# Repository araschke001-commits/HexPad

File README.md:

# HexPad
This is a macropad with 6 keys, a rotary encoder, and an oled display. Almost everything in the cad file for this project is customizable. You can add as many keys as you want, change the dimensions of the usb c port, the inside dimensions, the wall dimensions, and basically everything else.

You would use my project by pressing the keys to perform specific functions on the computer, like a simple key press like the number 1, or later I might change it to open a site or type a password in. The rotary encoder is to change volume and mute/unmute it. The oled display is to indicate if a button was pressed/changed.

The reason why I made this project is to learn how to build things like this project so in the future I can make other things similar to this.

## Features:
- 3d printed case
- 6 keys (2 rows of 3)
- 0.91" OLED display
- Rotary encoder
- Almost everything is customizable for the CAD design.

## CAD Model:
It is put together with 4 M3 Screws that go directly into the plastic of the case.

It is made of 2 separate 3d printed parts, the top and the bottom.

Here is the share link to the project: https://cad.onshape.com/documents/888c45d35c64a39055184245/w/6328c76e156d93114c845f2d/e/f25f9ae1fe243c3fda6125d5?renderMode=0&uiState=69c88a6d89ef4c064d381a0c

CAD Model:

Made in Onshape.

## PCB:
This PCB was made in KiCad.

Schematic:

PCB:

In hindsight, I maybe should have used a matrix to wire the switches, but it was simpler not to.

## Firmware:
This project uses C++ as firmware because I was unable to get the QMK firmware to work and I already had experience writing code in C++ (I did have to look up how to do some of the arduino stuff though).

The 6 keys act as a partial number pad for now. The oled is to display the last action, and the rotary encoder is to change volume and mute/unmute it.

## BOM:
This should be everything needed for my hackpad:
- Seeed Studio XIAO RP2040	(1x)
- Cherry MX Keycap - R2 (Opaque Black)	(6x)
- Cherry MX Brown 55g Tactile Switch	(6x)
- 0.91" OLED Display (1x)
- Rotary Encoder (1x)
- Rotary Encoder Knob (1x)
- M3 x 8mm Socket Button Head Screws	(4x)
- USB-C to USB-A Cable (3ft)	(1x)
- Custom PCB
- 3d Printed Case

## Build Guide
1. Order the components
2. Order the PCB
3. Solder the components onto the board
4. Move the firmware to the board using Arduino IDE
5. Put the pcb with everything attached in the case
6. Screw on the lid to the case

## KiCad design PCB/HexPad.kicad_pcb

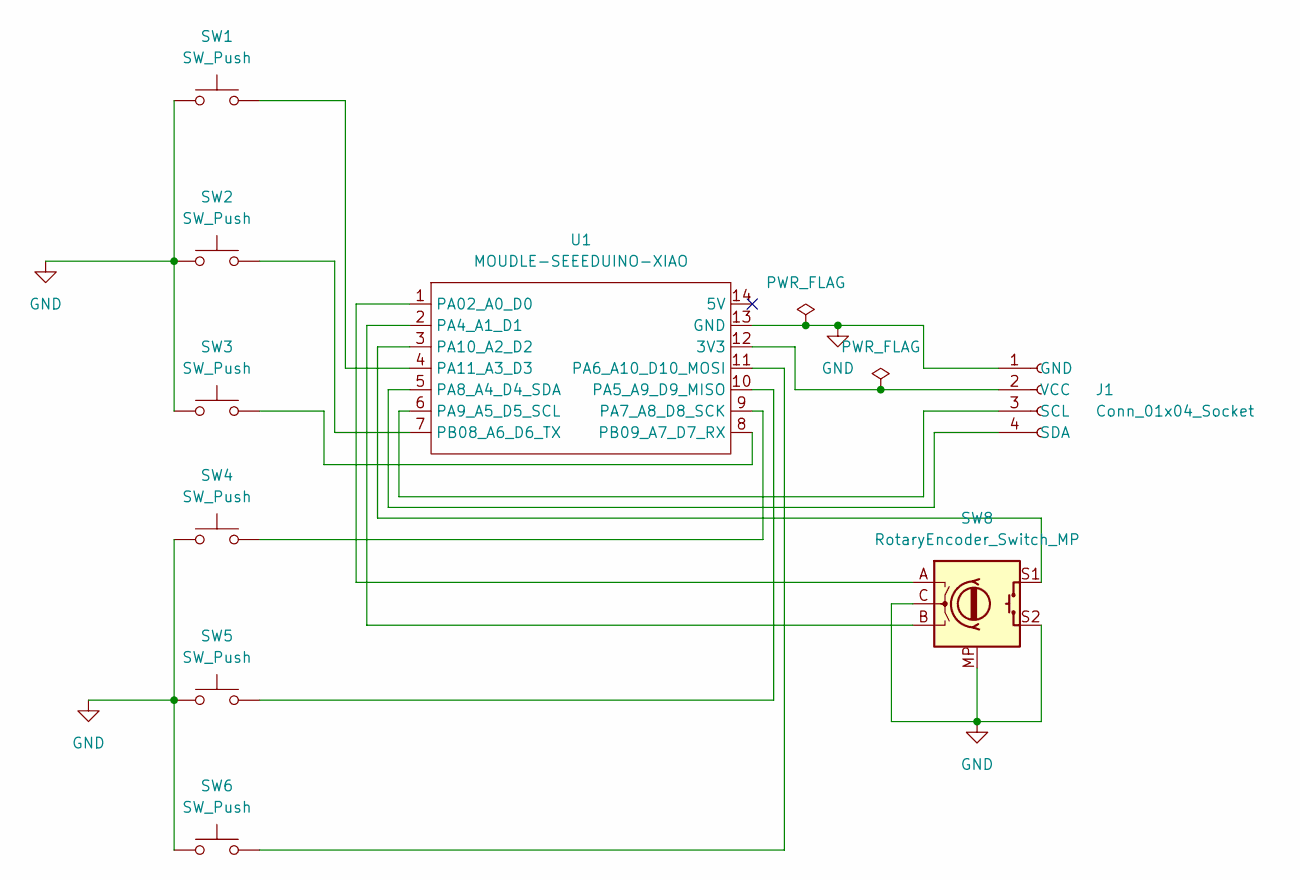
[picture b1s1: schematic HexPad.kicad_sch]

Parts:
J1: Conn_01x04_Socket; PinSocket_1x04_P2.54mm_Vertical
SW1, SW2, SW3, SW4, SW5, SW6: SW_Push; SW_Cherry_MX_1.00u_PCB
SW8: RotaryEncoder_Switch_MP; RotaryEncoder_Alps_EC11E-Switch_Vertical_H20mm
U1: MOUDLE-SEEEDUINO-XIAO; XIAO-Generic-Hybrid-14P-2.54-21X17.8MM

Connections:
GND: J1.1 (GND), SW1.1, SW2.1, SW3.1, SW4.1, SW5.1, SW6.1, SW8.C, SW8.MP, SW8.S2, U1.13 (GND)
unnamed: J1.3 (SCL), U1.6 (PA9_A5_D5_SCL)
unnamed: J1.4 (SDA), U1.5 (PA8_A4_D4_SDA)
unnamed: J1.2 (VCC), U1.12 (3V3)
unnamed: SW8.A, U1.1 (PA02_A0_D0)
unnamed: SW8.B, U1.2 (PA4_A1_D1)
unnamed: SW5.2, U1.10 (PA5_A9_D9_MISO)
unnamed: SW6.2, U1.11 (PA6_A10_D10_MOSI)
unnamed: SW4.2, U1.9 (PA7_A8_D8_SCK)
unnamed: SW8.S1, U1.3 (PA10_A2_D2)
unnamed: SW1.2, U1.4 (PA11_A3_D3)
unnamed: SW2.2, U1.7 (PB08_A6_D6_TX)
unnamed: SW3.2, U1.8 (PB09_A7_D7_RX)

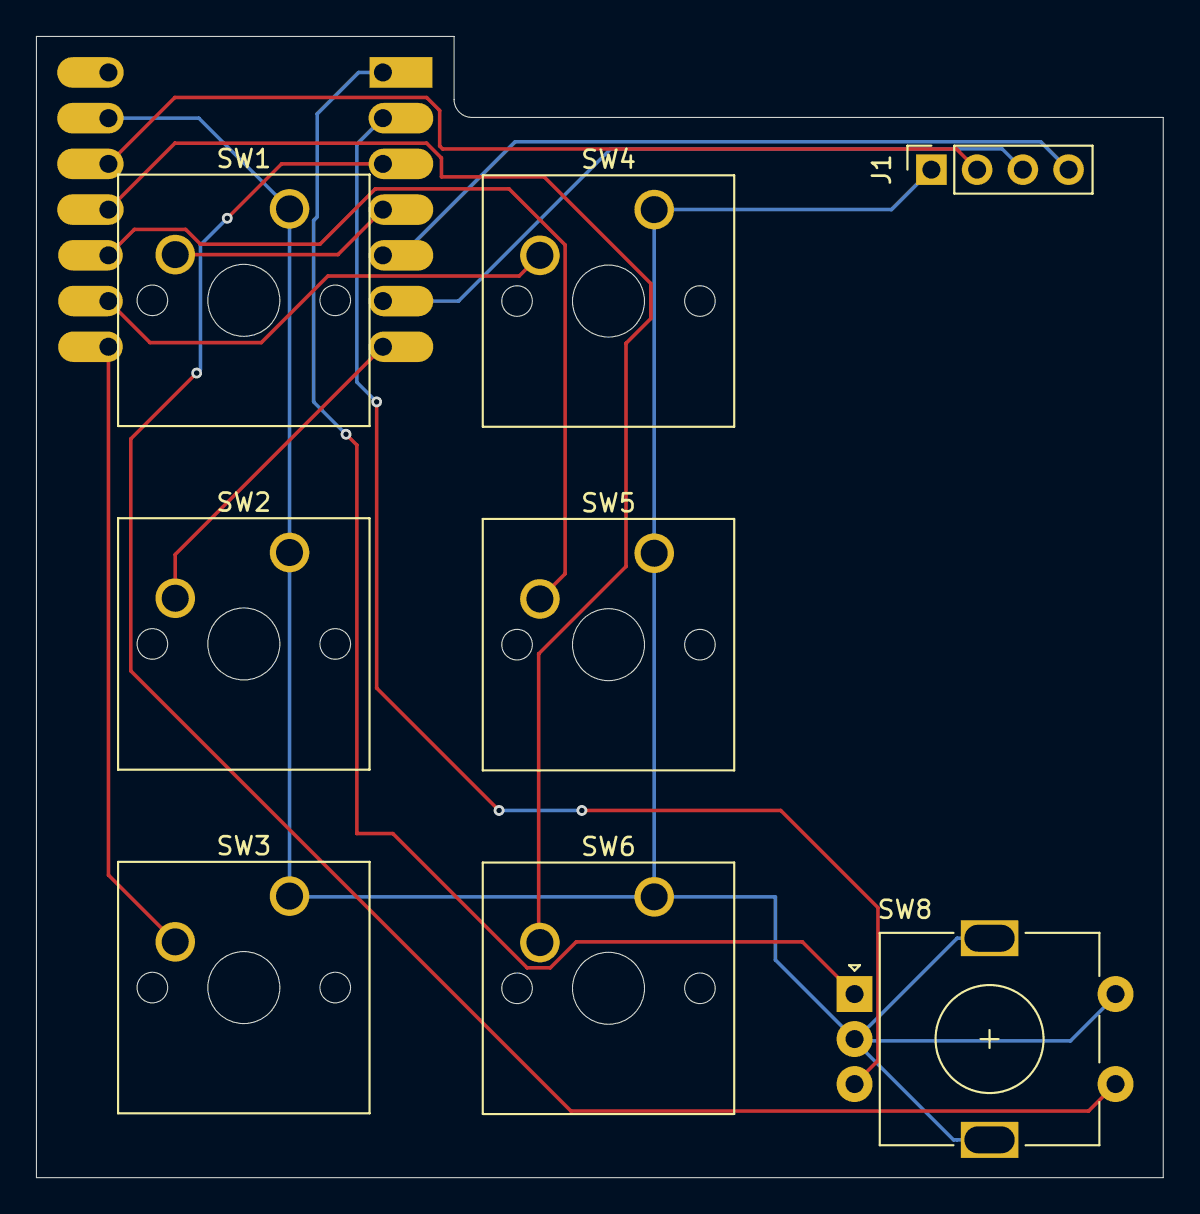
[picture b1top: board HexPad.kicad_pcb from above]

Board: 2 copper layers, 62.6 x 63.4 mm, 9 parts (1 on the bottom side), 13 nets.

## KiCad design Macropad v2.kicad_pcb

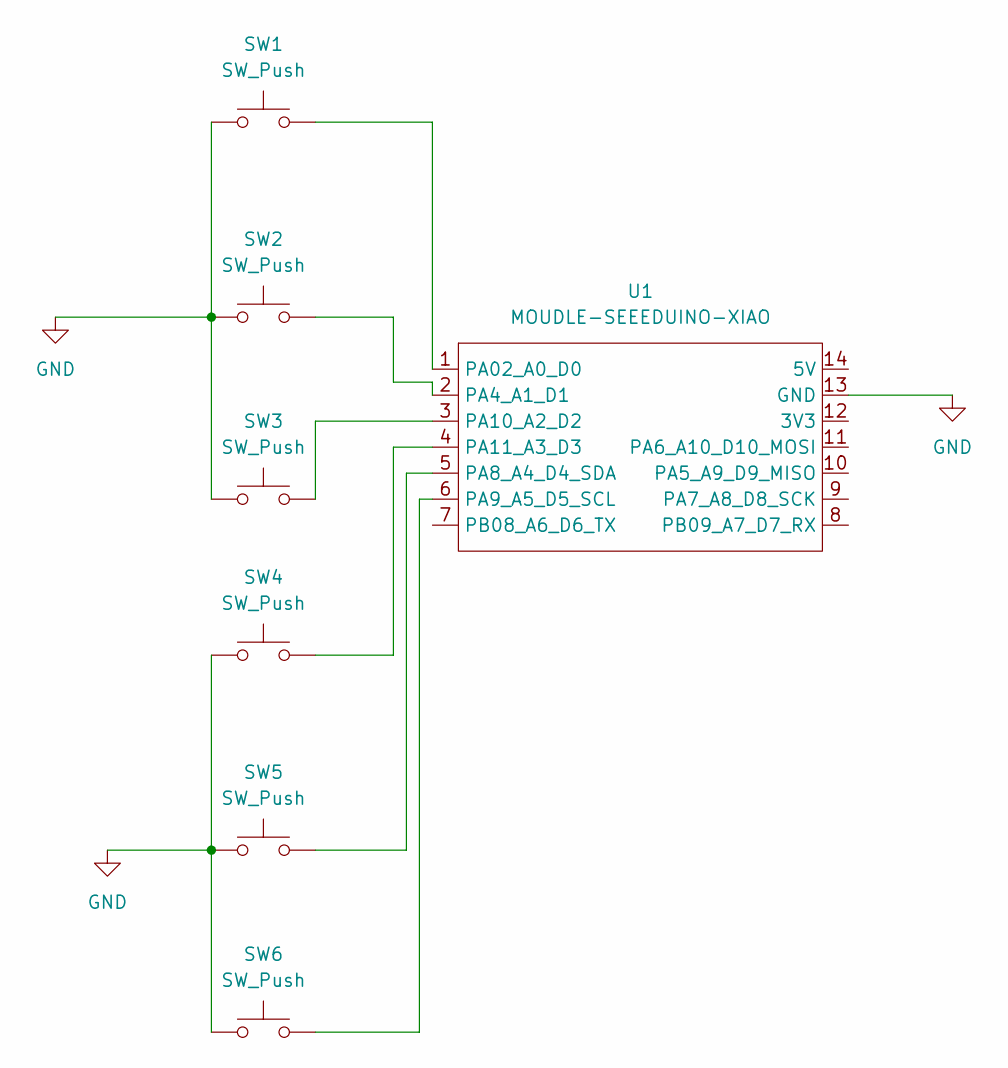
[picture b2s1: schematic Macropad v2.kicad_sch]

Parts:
SW1, SW2, SW3, SW4, SW5, SW6: SW_Push; SW_Cherry_MX_1.00u_PCB
U1: MOUDLE-SEEEDUINO-XIAO; XIAO-Generic-Hybrid-14P-2.54-21X17.8MM

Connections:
GND: SW1.1, SW2.1, SW3.1, SW4.1, SW5.1, SW6.1, U1.13 (GND)
unnamed: SW1.2, U1.1 (PA02_A0_D0)
unnamed: SW2.2, U1.2 (PA4_A1_D1)
unnamed: SW5.2, U1.5 (PA8_A4_D4_SDA)
unnamed: SW6.2, U1.6 (PA9_A5_D5_SCL)
unnamed: SW3.2, U1.3 (PA10_A2_D2)
unnamed: SW4.2, U1.4 (PA11_A3_D3)

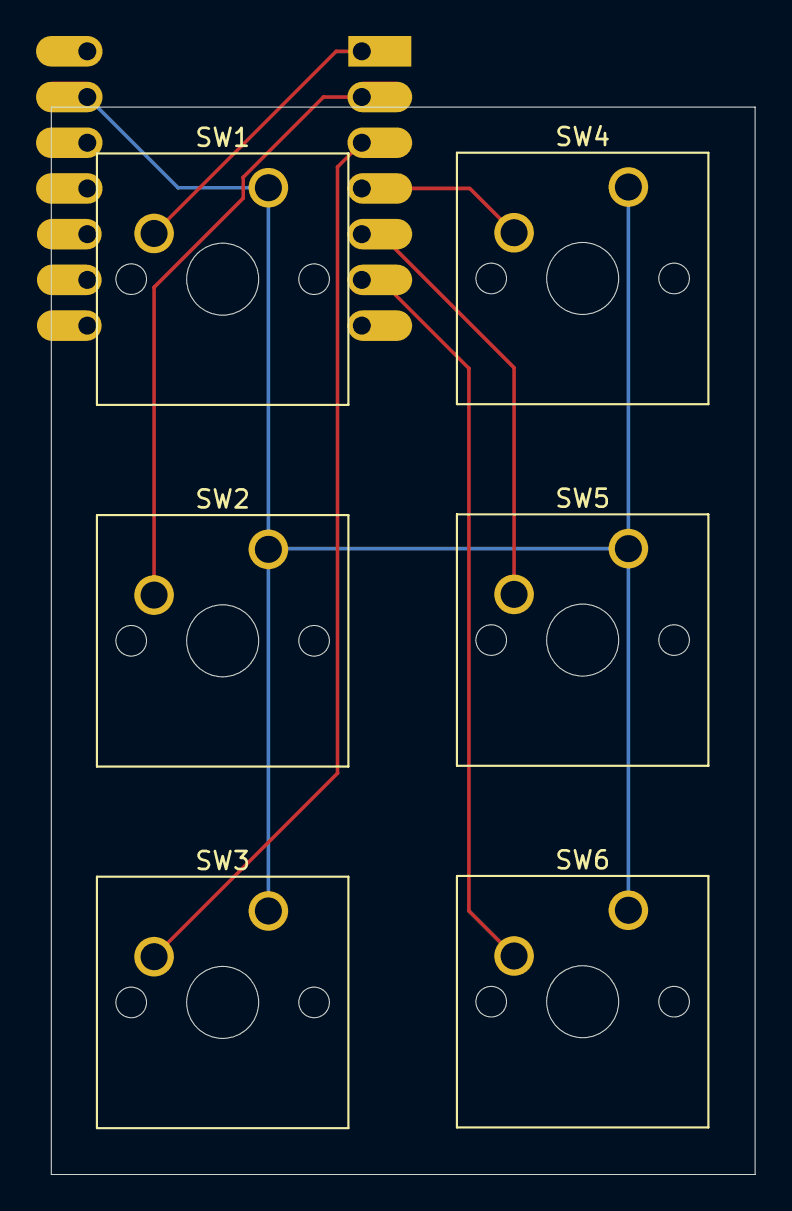
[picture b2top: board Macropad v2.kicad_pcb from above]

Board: 2 copper layers, 39.1 x 59.3 mm, 7 parts (1 on the bottom side), 7 nets.

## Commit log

2026-03-29 Create C++ Firmware
2026-03-29 Update C++ Firmware
2026-03-29 Create Bill of Materials
2026-03-30 Create TEMP
2026-03-30 Rename Macropad v2.kicad_pcb to PCB/Macropad v2.kicad_pcb
2026-03-30 Rename Macropad v2.kicad_pro to PCB/Macropad v2.kicad_pro
2026-03-30 Rename Macropad v2.kicad_sch to PCB/Macropad v2.kicad_sch
2026-03-30 Rename folder firmware to Firmware
2026-03-30 Create Full Assembly
2026-03-30 Create Top Part
2026-04-07 Update README.md Picture
2026-04-07 Include OLED in BOM.csv
2026-04-07 Fix BOM.csv
2026-04-08 Update BOM Total
2026-04-08 Removing Options from BOM.csv
2026-04-08 Clean BOM.csv
2026-04-08 Swap Firmware/C++ Firmware.cpp
2026-04-08 Swap Firmware
2026-04-11 Update Total
2026-04-13 Add Knob
2026-04-13 Remove Ambiguity
